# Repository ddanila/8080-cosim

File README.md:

# 8080-cosim

Reconstruction of the Soviet/Estonian Juku E5104 processor board as a physical
PCB and a runnable digital model. Structural Verilog connectivity is checked
against the machine-readable board model with LVS.

## Emulator dependency

The portable C emulator is maintained in [dac-emulation](https://github.com/ddanila/dac-emulation), pinned here as a submodule. After cloning or pulling, run:

```sh
git submodule update --init third_party/dac-emulation
```

Existing `cosim/*.c` build commands still work through forwarding files. Hardware models and their verification stay here. See [the consumer guide](cosim/README.md) for ownership and updating the pin. `bash sync/emulation_check.sh` runs fast native checks without Verilog.

## Current state

The C emulator and structural `juku_top` have ROM-boot and framebuffer
comparison guards, plus keyboard, CPU, FDC, serial and subsystem checks.
The deep cosim guard compares typed CPU-bus events against the C oracle.

The C emulator boots the vendored EKDOS images and reaches disk BASIC
`READY`. [Recorded HDL runs](docs/juku-top-jbasic-verilator-probe.md) also
reached that prompt; current Verilator reruns have a
[build compatibility limitation](sync/README.md#simulator-compatibility).
The bounded boot guard does not establish the full EKDOS/BASIC prompt path.

The production network host is portable C. Linux/macOS, DOS and the Windows
GUI share its core; Janet, Fastboot, NetDisk, N4, snapshots, journals and reset
recovery are implemented. See the [host contract](docs/portable-c-host-plan.md)
and [Windows guide](docs/windows-jukuhost-client.md) for platform qualification
and the latest build.

The physical board is on **DESIGN HOLD / PACKAGE REGENERATION REQUIRED**.
Hidden or conflicting source paths, physical placement, routed copper and
parts decisions remain. The evidence archive is a review package, and the
current Gerber/drill upload ZIP is absent. The
[manufacturing report](docs/replica-manufacturing-readiness.md) owns release
status; [PLAN.md](PLAN.md) lists the remaining work.

The physical shared-DRAM/video slot schedule is not complete. The runnable
framebuffer readout is an abstract oracle, not a proved VIDEO_OUT voltage
waveform. Green behavioral CI and LVS do not establish physical authenticity.

The independent spin-offs are [Jukuravi](spinoffs/jukuravi/README.md),
[VJUGA](spinoffs/minimal-vga/README.md) and
[JukuPoly](spinoffs/jukupoly/README.md). Their physical results and release
criteria are separate from the replica main board.

## Network boot demonstrations

These simulator captures pair the native Juku framebuffer on the left with
timestamped Janet host activity on the right. The simulator is paced at the
approximately 1.7 MHz effective CPU execution rate, the serial links use their
stated baud rates. GIF playback approximates the presentation timeline;
framebuffer timestamp normalization and delay quantization are described in
[the capture guide](media/demos/README.md).

### Stock ROM and CP/Mish CP/M 2.2

The archival 9,600-baud Janet bootstrap is intentionally shown at its original
speed.

### Historical stock-ROM CP/M Plus fast bootstrap

This frozen Python-era V15 capture records the unmodified-ROM experiment whose
compact loader switched to 19,200 baud. The exact JF15 protocol is now
supported by the C host for stock-ROM compatibility, but this historical GIF
itself is not regenerated by the current demo runner.

### Network ROM and CP/M Plus tools

The C8 network-first ROM boots CP/M Plus 3.1 through Fastboot V16 and
demonstrates the resident version report, text utilities, command history, and
control panel.

The capture inputs, dependencies, and regeneration commands are documented in
[`media/demos/README.md`](media/demos/README.md).

## Downstream smoke kit

Use `ghcr.io/ddanila/8080-cosim-smoke-kit:v2` to obtain simulator artifacts
without cloning the repository. The Linux amd64 kit contains the simulator,
static `jukuhost`, frozen Python test fixtures and three ROMs, listed in
[its manifest](.github/smoke-kit/smoke-kit.json) at
`/opt/8080-cosim/smoke-kit.json`.

The `scratch` image has no shell or simulator shared libraries. Copy its
artifacts into a Linux amd64 runtime with the required dynamic loader and
libraries; the [Dockerfile](.github/smoke-kit/Dockerfile) uses Ubuntu 24.04.
The Python fixtures are not standalone executables.

[Publishing](.github/workflows/smoke-kit.yml) runs for selected input changes
on `master` or manual dispatch. It produces the moving `v2` tag and a
`sha-<source commit>` tag. Pin an image digest for reproducible inputs.

## Evidence and source hierarchy

1. Factory drawings, board photographs, dumps, and owner measurements under
   `ref/` are the historical evidence.
2. `kicad/juku.board.json` is the current machine-readable connectivity model.
3. `kicad/juku.kicad_sch`, the PCB files, and fabrication outputs are derived
   from or checked against that model.
4. `hdl/juku_top.v` is independently maintained structural Verilog and is
   checked against the modeled connectivity by `sync/`.
5. `cosim/` and the vendored MAME Juku driver (`ref/mame_juku.cpp`) are behavioral references;
   they are not substitutes for missing physical wiring evidence.

## Board previews

These saved renders show a routed engineering snapshot and may lag the current
PCB. Refresh them with `kicad/render_views.sh` after reviewing board changes;
the [renderer](kicad/render_views.sh) documents its KiCad, font and rasterizer
requirements. Use the PCB and release reports to assess the current design.

| 3D | 2D |
| --- | --- |
|  |  |
|  |  |

## Useful entry points

- [PLAN.md](PLAN.md) — remaining work and release criteria.
- [docs/README.md](docs/README.md) — documentation map and generated-report
  policy.
- [docs/development-workflow.md](docs/development-workflow.md) — canonical
  branch, intermediate commit, and direct-push policy.
- [docs/git-lfs-policy.md](docs/git-lfs-policy.md) — preservation and
  bandwidth policy for original reference photographs.
- [docs/architecture.md](docs/architecture.md) — model boundaries and data flow.
- [docs/source-coverage-audit.md](docs/source-coverage-audit.md) — adopted
  external evidence and remaining source gaps.
- [sync/README.md](sync/README.md) — verification commands.
- [docs/replica-manufacturing-readiness.md](docs/replica-manufacturing-readiness.md)
  — fabrication-package integrity and the current design hold.

## Verification commands

```sh
sync/check.sh
sync/boot_check.sh
sync/cosim_check.sh
python3 scripts/check_documentation_consistency.py
```

`sync/cosim_check.sh` is a deep guard and can take substantially longer than
the other commands. The long reset-to-EKDOS/BASIC and Monitor 3.3 diagnostics
have separate entry points listed in `sync/README.md`.

## Layout

| Path | Purpose |
| --- | --- |
| `ref/` | Factory drawings, photographs, firmware evidence, and external references |
| `kicad/` | Board model, generated schematic, source/routed PCBs with current routing holds, and fabrication tooling |
| `hdl/` | Structural runnable model and device behavior |
| `cosim/` | Independent software emulator/oracle |
| `sync/` | LVS, behavioral comparisons, and subsystem guards |
| `roms/`, `media/` | Vendored preservation inputs with provenance/checksums |
| `docs/` | Current specifications and generated evidence reports |
| `spinoffs/jukupoly/` | Independent Juku CP/M three-tone-plus-percussion music engine, importers, songs, and evidence |
| `spinoffs/minimal-vga/` | Independent VJUGA experiment; not on the replica critical path |

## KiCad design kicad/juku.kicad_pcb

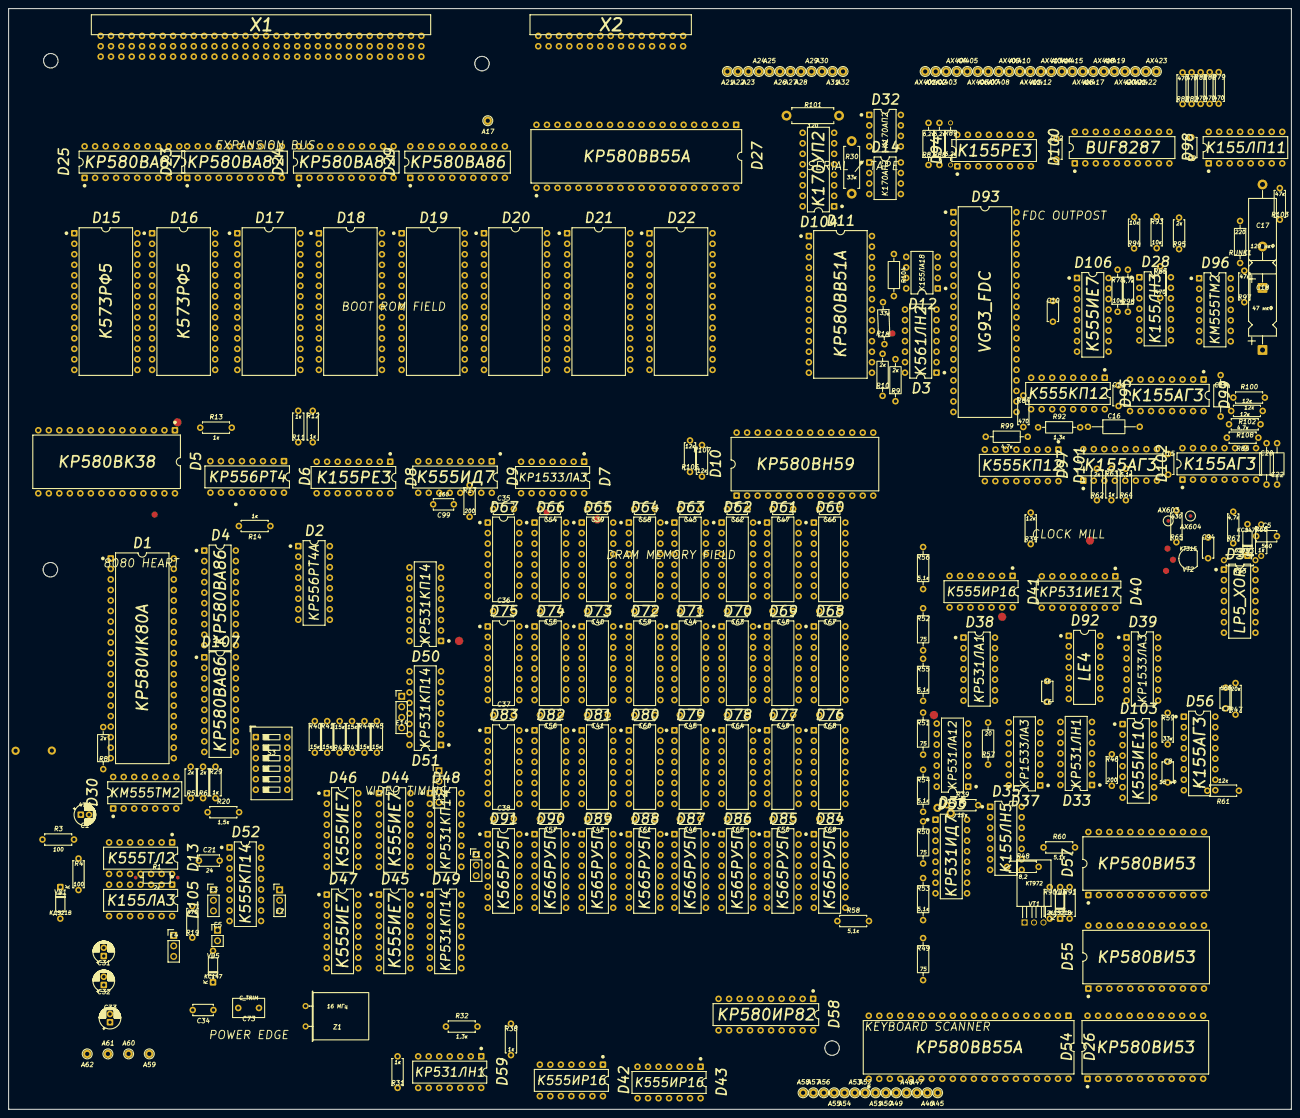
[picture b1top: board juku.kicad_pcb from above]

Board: 2 copper layers, 310.0 x 266.0 mm, 324 parts (0 on the bottom side), 418 nets, no tracks yet.

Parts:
A17, A21, A22, A23, A24, A25, A26, A27, A28, A29, A30, A31, A32, A45, A46, A47, A48, A49, A50, A51, A52, A53, A54, A55, A56, A57, A58, A59, A60, A61, A62: TestPoint_THTPad_D2.0mm_Drill1.0mm
AX401, AX402, AX403, AX404, AX405, AX406, AX407, AX408, AX409, AX410, AX411, AX412, AX413, AX414, AX415, AX416, AX417, AX418, AX419, AX420, AX421, AX422, AX423, AX603, AX604: TestPoint_THTPad_D2.0mm_Drill1.0mm
C1: 47,0; CP_Radial_D5.0mm_P2.00mm
C5, C7: 560; C_Disc_D4.7mm_W2.5mm_P5.00mm
C6: 56; C_Disc_D4.7mm_W2.5mm_P5.00mm
C8: 15 нФ; C_Disc_D4.7mm_W2.5mm_P5.00mm
C9, C10, C11, C12, C15, C34, C94: C_Disc_D4.7mm_W2.5mm_P5.00mm
C16: C_Axial_L5.1mm_D3.1mm_P12.50mm_Horizontal
C17: 120 мкФ; CP_Axial_L18.0mm_D6.5mm_P25.00mm_Horizontal
C18: 47 мкФ; CP_Axial_L18.0mm_D6.5mm_P25.00mm_Horizontal
C19, C20, C22: C_Axial_L5.1mm_D3.1mm_P10.00mm_Horizontal
C21: 24; C_Disc_D4.7mm_W2.5mm_P5.00mm
C31, C32, C33: CP_Radial_D5.0mm_P2.00mm
C35, C36, C37, C38, C39, C40, C41, C42, C43, C44, C45, C46, C47, C48, C49, C50, C54, C55, C56, C57, C58, C59, C60, C61, C62, C63, C64, C65, C66, C67, C68, C69: 0,047; C_Disc_D4.7mm_W2.5mm_P5.00mm
C73: C_TRIM; C_Disc_D7.5mm_W4.4mm_P5.00mm
C99: 160; C_Disc_D4.7mm_W2.5mm_P5.00mm
D1: КР580ИК80А; DIP-40_W15.24mm
D2: КР556РТ4А; DIP-16_W7.62mm
D3: К561ЛН2; DIP-14_W7.62mm
D4, D29, D107: КР580ВА86; DIP-20_W7.62mm
D5: КР580ВК38; DIP-28_W15.24mm
D6: КР556РТ4; DIP-16_W7.62mm
D7, D37, D39: КР1533ЛА3; DIP-14_W7.62mm
D8, D94: К155РЕ3; DIP-16_W7.62mm
D9: К555ИД7; DIP-16_W7.62mm
D10: КР580ВН59; DIP-28_W15.24mm
D11: КР580ВВ51А; DIP-28_W15.24mm
D12: К155ЛА18; DIP-8_W7.62mm
D13: К555ТЛ2; DIP-14_W7.62mm
D14, D32: К170АП2; DIP-8_W7.62mm
D15, D16, D17, D18, D20, D21, D22: К573РФ5; DIP-28_W15.24mm
D19: К573РФ6; DIP-28_W15.24mm
D23, D24, D25: КР580ВА87; DIP-20_W7.62mm
D26, D27: КР580ВВ55А; DIP-40_W15.24mm
D28: К155ЛН3; DIP-14_W7.62mm
D30, D96: КМ555ТМ2; DIP-14_W7.62mm
D33, D59: КР531ЛН1; DIP-14_W7.62mm
D34: LP5_XOR; DIP-14_W7.62mm
D35: К155ЛН5; DIP-14_W7.62mm
D36: КР531ЛА12; DIP-14_W7.62mm
D38: КР531ЛА1; DIP-14_W7.62mm
D40: КР531ИЕ17; DIP-16_W7.62mm
D41, D42, D43: К555ИР16; DIP-14_W7.62mm
D44, D45, D46, D47, D106: К555ИЕ7; DIP-16_W7.62mm
D48, D49, D50, D51: КР531КП14; DIP-16_W7.62mm
D52: К555КП14; DIP-16_W7.62mm
D53: КР531ИД7; DIP-16_W7.62mm
D54, D55, D57: КР580ВИ53; DIP-24_W15.24mm
D56, D97, D99, D102: К155АГ3; DIP-16_W7.62mm
D58: КР580ИР82; DIP-20_W7.62mm
D60, D61, D62, D63, D64, D65, D66, D67, D68, D69, D70, D71, D72, D73, D74, D75, D76, D77, D78, D79, D80, D81, D82, D83: 565РУ3Г; DIP-16_W7.62mm
D84, D85, D86, D87, D88, D89, D90, D91: К565РУ5Г; DIP-16_W7.62mm
D92: LE4; DIP-14_W7.62mm
D93: VG93_FDC; DIP-40_W15.24mm
D95, D101: К555КП12; DIP-16_W7.62mm
D98: К155ЛП11; DIP-16_W7.62mm
D100: BUF8287; DIP-20_W7.62mm
D103: К555ИЕ10; DIP-16_W7.62mm
D104: К170УП2; DIP-16_W7.62mm
D105: К155ЛА3; DIP-14_W7.62mm
E1, E2, E3, E4: PinHeader_1x03_P2.54mm_Vertical
E5: PinHeader_1x02_P2.54mm_Vertical
E13, E14: PinHeader_1x04_P2.54mm_Vertical
R1, R8, R9, R10: 2к; R_Axial_DIN0207_L6.3mm_D2.5mm_P10.16mm_Horizontal
R3, R4: 100; R_Axial_DIN0207_L6.3mm_D2.5mm_P7.62mm_Horizontal
R5, R6, R62, R90, R95: 2к; R_Axial_DIN0207_L6.3mm_D2.5mm_P7.62mm_Horizontal
R11, R12, R13, R14, R29, R31, R38, R63, R66, R91: 1к; R_Axial_DIN0207_L6.3mm_D2.5mm_P7.62mm_Horizontal
R17, R46: 200; R_Axial_DIN0207_L6.3mm_D2.5mm_P7.62mm_Horizontal
R18: 33к; R_Axial_DIN0207_L6.3mm_D2.5mm_P10.16mm_Horizontal
R19, R79, R80, R81, R82, R83, R84, R85: 470; R_Axial_DIN0207_L6.3mm_D2.5mm_P7.62mm_Horizontal
R20: 1,5к; R_Axial_DIN0207_L6.3mm_D2.5mm_P7.62mm_Horizontal
R30: 33к; R_Axial_DIN0411_L9.9mm_D3.6mm_P12.70mm_Horizontal
R32: 1,3к; R_Axial_DIN0207_L6.3mm_D2.5mm_P7.62mm_Horizontal
R33: 620; R_Axial_DIN0207_L6.3mm_D2.5mm_P7.62mm_Horizontal
R34, R39, R61, R100, R102, R105, R107, R108: 12к; R_Axial_DIN0207_L6.3mm_D2.5mm_P7.62mm_Horizontal
R40, R41, R42, R43, R44, R45: 15к; R_Axial_DIN0207_L6.3mm_D2.5mm_P7.62mm_Horizontal
R47: 20к; R_Axial_DIN0207_L6.3mm_D2.5mm_P7.62mm_Horizontal
R48: 8,2; R_Axial_DIN0207_L6.3mm_D2.5mm_P7.62mm_Horizontal
R49, R50, R51, R52: 75; R_Axial_DIN0207_L6.3mm_D2.5mm_P10.16mm_Horizontal
R53, R54, R55, R56: 5,1к; R_Axial_DIN0207_L6.3mm_D2.5mm_P10.16mm_Horizontal
R57: 20; R_Axial_DIN0207_L6.3mm_D2.5mm_P10.16mm_Horizontal
R58, R60, R64: 5,1к; R_Axial_DIN0207_L6.3mm_D2.5mm_P7.62mm_Horizontal
R59: 33к; R_Axial_DIN0207_L6.3mm_D2.5mm_P7.62mm_Horizontal
R65: 430; R_Axial_DIN0207_L6.3mm_D2.5mm_P7.62mm_Horizontal
R67, R86: 4,7к; R_Axial_DIN0207_L6.3mm_D2.5mm_P7.62mm_Horizontal
R78: 10к; R_Axial_DIN0207_L6.3mm_D2.5mm_P10.16mm_Horizontal
R87, R88, R89: 6,2к; R_Axial_DIN0207_L6.3mm_D2.5mm_P10.16mm_Horizontal
R92: 1,3к; R_Axial_DIN0207_L6.3mm_D2.5mm_P10.16mm_Horizontal
R93, R94: 10к; R_Axial_DIN0207_L6.3mm_D2.5mm_P7.62mm_Horizontal
R97, R103: 47к; R_Axial_DIN0207_L6.3mm_D2.5mm_P7.62mm_Horizontal
R98, R99: 4,7к; R_Axial_DIN0207_L6.3mm_D2.5mm_P10.16mm_Horizontal
R101: 120; R_Axial_DIN0411_L9.9mm_D3.6mm_P12.70mm_Horizontal
R104: 470; R_Axial_DIN0207_L6.3mm_D2.5mm_P10.16mm_Horizontal
RUNK1: 220; R_Axial_DIN0207_L6.3mm_D2.5mm_P10.16mm_Horizontal
S3: SW_DIP_SPSTx06_Slide_9.78x17.42mm_W7.62mm_P2.54mm
VD1, VD4: КД521В; D_DO-35_SOD27_P7.62mm_Horizontal
VD3: КС147Г; D_DO-35_SOD27_P7.62mm_Horizontal
VD5: КС147; D_DO-35_SOD27_P7.62mm_Horizontal
VT1: КТ972; TO-126-3_Horizontal_TabDown
VT2: КТ315; TO-92_Inline
W7: A:7 ~24cm insulated wire (cut length held); FACTORY_WIRE_W7
W8: A:8 ~19cm insulated wire; FACTORY_WIRE_W8
W10: A:10 13.5cm insulated wire; FACTORY_WIRE_W10
W11: A:11 ~11.5cm insulated wire (cut length held); FACTORY_WIRE_W11
W14: A:14 ~23cm insulated wire (cut length held); FACTORY_WIRE_W14
W19: A:19 ~9.5cm insulated wire; FACTORY_WIRE_W19
W20: A:20 ~6cm insulated wire; FACTORY_WIRE_W20
X1: CONN_X1
X2: CONN_X2
Z1: 16 МГц; Crystal_HC49-U_Horizontal

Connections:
A0: D1.25, D107.1
A1: D1.26, D107.2
A2: D1.27, D107.3
A3: D1.29, D107.4
A4: D1.30, D107.5
A5: D1.31, D107.6
A6: D1.32, D107.7
A7: D1.33, D107.8
A8: D1.34, D4.8
A9: D1.35, D2.7, D4.7
A10: D1.1, D2.1, D4.1
A11: D1.40, D4.2
A12: D1.37, D2.5, D4.5
A13: D1.38, D4.4
A14: D1.39, D2.3, D4.3
A15: D1.36, D2.6, D4.6
ADR0_N: D23.19, X1.124C
ADR1_N: D23.18, X1.124B
ADR2_N: D23.17, X1.123C
ADR3_N: D23.16, X1.123B
ADR4_N: D23.15, X1.122C
ADR5_N: D23.14, X1.122B
ADR6_N: D23.13, X1.121C
ADR7_N: D23.12, X1.121B
ADR8_N: D24.19, X1.120C
ADR9_N: D24.18, X1.120B
ADRA_N: D24.17, X1.119C
ADRB_N: D24.16, X1.119B
ADRC_N: D24.15, X1.118C
ADRD_N: D24.14, X1.118B
ADRE_N: D24.13, X1.117C
ADRF_N: D24.12, X1.117B
AMWC_N: D29.12, X1.102B
AMW_N: D7.3, D29.2
AVDC: D26.40, R91.2
BA0: D10.27, D11.12, D15.10, D16.10, D17.10, D18.10, D19.10, D20.10, D21.10, D22.10, D23.1, D26.9, D27.9, D48.2, D54.19, D55.19, D57.19, D93.5, D94.10, D107.19
BA1: D15.9, D16.9, D17.9, D18.9, D19.9, D20.9, D21.9, D22.9, D23.2, D26.8, D27.8, D48.14, D54.20, D55.20, D57.20, D93.6, D94.11, D107.18
BA2: D15.8, D16.8, D17.8, D18.8, D19.8, D20.8, D21.8, D22.8, D23.3, D48.11, D107.17
BA3: D15.7, D16.7, D17.7, D18.7, D19.7, D20.7, D21.7, D22.7, D23.4, D48.5, D107.16
BA4: D15.6, D16.6, D17.6, D18.6, D19.6, D20.6, D21.6, D22.6, D23.5, D49.2, D107.15
BA5: D15.5, D16.5, D17.5, D18.5, D19.5, D20.5, D21.5, D22.5, D23.6, D49.14, D107.14
BA6: D15.4, D16.4, D17.4, D18.4, D19.4, D20.4, D21.4, D22.4, D23.7, D49.11, D107.13
BA7: D15.3, D16.3, D17.3, D18.3, D19.3, D20.3, D21.3, D22.3, D23.8, D49.5, D52.2, D107.12
BA8: D4.12, D15.25, D16.25, D17.25, D18.25, D19.25, D20.25, D21.25, D22.25, D24.1, D49.6, D52.5
BA9: D4.13, D15.24, D16.24, D17.24, D18.24, D19.24, D20.24, D21.24, D22.24, D24.2, D48.3
BA10: D4.19, D9.1, D15.21, D16.21, D17.21, D18.21, D19.21, D20.21, D21.21, D22.21, D24.3, D48.6
BA11: D4.18, D6.3, D8.10, D9.2, D15.23, D16.23, D17.23, D18.23, D19.23, D20.23, D21.23, D22.23, D24.4, D48.10
BA12: D4.15, D6.4, D8.11, D9.3, D15.2, D16.2, D17.2, D18.2, D19.2, D20.2, D21.2, D22.2, D24.5, D49.3
BA13: D4.16, D6.7, D8.12, D24.6, D48.13
BA14: D4.17, D6.6, D8.13, D24.7, D49.13
BA15: D4.14, D6.5, D8.14, D24.8, D49.10
C21_R20_SERIES: C21.2, R20.1
CAS: D2.4, D36.1, D38.1, D60.15, D61.15, D62.15, D63.15, D64.15, D65.15, D66.15, D67.15, D68.15, D69.15, D70.15, D71.15, D72.15, D73.15, D74.15, D75.15, D76.15, D77.15, D78.15, D79.15, D80.15, D81.15, D82.15, D83.15, D84.15, D85.15, D86.15, D87.15, D88.15, D89.15, D90.15, D91.15, R57.2, R58.1
CAS_PRE: D36.11, R57.1
CCLCK: D29.19, X1.111C
CLKG_D33: D33.8, D38.9
CLKG_D36: D35.11, D36.6
CLK_123M: D57.9, D103.11
CO0: D44.12, D45.5
CO1: D45.12, D46.5
CO2: D46.12, D47.5
CPU_MUX_G: D48.15, D49.15, D59.6, E13.1, E13.3
CS_D10: D9.15, D10.1
CS_D11: D9.13, D11.11
CS_D26: D9.14, D26.6
CS_D27: D9.12, D27.6
CS_D54: D9.11, D54.21
CS_D55: D9.10, D55.21
CS_D57: D9.9, D57.21
CTR_LD: D34.3, D44.11, D45.11
D3_O4_D6_A6: D3.4, D6.1
D3_O6_D6_A5: D3.6, D6.2
D6_V_ENABLE: D6.13, D6.14, D13.12
D13_4_D105_2: D11.20, D13.4, D30.11, D105.2
D25_T: D7.6, D25.11
D26_PC0_D3_I5: D3.5, D26.14
D26_PC1_D3_I3: D3.3, D26.15
D30_Q2N_D29_AIN7: D29.7, D30.8
D33_6_D36: D33.6, D36.4
D33_CLK_RC: C6.1, D33.9, R46.2
D33_D36: D33.10, D36.10
D33_O4: D33.4, D37.5
D34_RC_DRIVE: C5.1, D34.6
D34_RC_NODE: C5.2, D34.2, R33.1
D34_SIG: D34.11, R63.1
D34_SYNC: D34.8, R62.1
D36_CAS_IN: D36.12, D36.13
D36_D33: D33.11, D36.3
D39Y: D38.10, D38.13, D39.11
D39_MEMCYC: D39.3, D39.4
D39_O8: D39.8, D59.11
D40Q1_D39: D36.5, D39.12, D40.13, D95.11, D95.12, D95.13
D40Q2_D33: D33.5, D40.12, D57.15, D95.3, D95.4
D40QA: D39.13, D40.14, D95.10, R46.1
D40_CTRL_PULL: D40.1, D40.9, R34.2
D42_Q: D35.4, D37.13, D42.10
D43_DS: D42.1, D43.10
D52_Y0: D52.4, E2.1
D52_Y1: D52.7, E3.1
D53_Y0_R49: D53.15, R49.1
D53_Y1_R50: D53.14, R50.1
D53_Y2_R51: D53.13, R51.1
D53_Y3_R52: D53.12, R52.1
D56_C1: C8.2, D56.14
D56_C2: C7.2, D56.6
D56_CLR: D56.3, D56.11, R61.2
D56_Q2N_TAG16: D55.15, D55.18, D56.12
D56_Q2_D34: D34.9, D56.5
D56_QN_D34: D34.10, D56.4
D56_RC1: C8.1, D56.15, R59.1
D56_RC2: C7.1, D56.7, R47.1
D92_NOACC: D39.5, D92.8
D92_RD_NOR: D92.11, D92.12
D92_WR_NOR: D92.6, D92.9, D92.10
D93_TEST_WF_VFOE: D93.22, D93.33
D94_A4_D101_Q0: D94.14, D101.7
D94_D0_BOUNDARY: D94.1, R8.1
D94_D1_D99_A2N: D94.2, D96.11, D99.9, R89.1
D96_TOGGLE_FEEDBACK: D96.2, D96.6
D97_C1_C16: C16.2, D97.14
D97_C2_C19_R86_TARGET: C19.2, D97.6, R86.1
D97_RC1_C16: C16.1, D97.15
D97_RC2_C19_R100: C19.1, D97.7, R100.1
D98_Y1_D28_READY: D28.5, D98.3
D98_Y3_S1_2: D97.2, D98.7
D99_B2_SHEET1_BOUNDARY: D96.13, D99.10
D99_C1_TIMING: C18.2, D99.14
D99_C2_TIMING: C17.2, D99.6
D99_Q1N_BOUNDARY: D93.23, D99.4
D99_Q2N_BOUNDARY: D99.12, D100.9
D99_Q2_BOUNDARY: D99.5, D100.7
D99_RC1_TIMING: C18.1, D99.15, R103.1
D99_RC2_TIMING: C17.1, D99.7, R97.1
D101_D02_R92_R99: D96.9, D101.3, D101.4, D101.5, D101.6, R92.1, R99.2
D102_C1_C22: C22.1, D102.14
D102_C2_C20: C20.1, D102.6
D102_RC1_C22_R102: C22.2, D102.15, R102.1
D102_RC2_C20_R108: C20.2, D102.7, R108.1
D103_CO: D33.1, D103.15
D103_LD: D33.2, D103.9
D105_10_H: D13.13, D105.10, R1.2, X1.107B
D105_MEMW_INV: D30.13, D105.11
D105_WAIT_STAGE: D105.4, D105.5, D105.8
D106_PRESET_HIGH: D106.1, D106.5, D106.9, D106.10, D106.15, R78.1
DAT0_N: D25.19, X1.132C
DAT1_N: D25.18, X1.132B
DAT2_N: D25.17, X1.131C
DAT3_N: D25.16, X1.131B
DAT4_N: D25.15, X1.130C
DAT5_N: D25.14, X1.130B
DAT6_N: D25.13, X1.129C
DAT7_N: D25.12, X1.129B
DB0: D5.18, D10.11, D11.27, D15.11, D16.11, D17.11, D18.11, D19.11, D20.11, D21.11, D22.11, D25.1, D26.34, D27.34, D54.8, D55.8, D57.8, D58.19, D60.2, D68.2, D76.2, D84.2, D93.7
DB1: D5.16, D10.10, D11.28, D15.12, D16.12, D17.12, D18.12, D19.12, D20.12, D21.12, D22.12, D25.2, D26.33, D27.33, D54.7, D55.7, D57.7, D58.18, D61.2, D69.2, D77.2, D85.2, D93.8
DB2: D5.9, D10.9, D11.1, D15.13, D16.13, D17.13, D18.13, D19.13, D20.13, D21.13, D22.13, D25.3, D26.32, D27.32, D54.6, D55.6, D57.6, D58.17, D62.2, D70.2, D78.2, D86.2, D93.9
DB3: D5.20, D10.8, D11.2, D15.15, D16.15, D17.15, D18.15, D19.15, D20.15, D21.15, D22.15, D25.4, D26.31, D27.31, D54.5, D55.5, D57.5, D58.16, D63.2, D71.2, D79.2, D87.2, D93.10
DB4: D5.5, D10.7, D11.5, D15.16, D16.16, D17.16, D18.16, D19.16, D20.16, D21.16, D22.16, D25.5, D26.30, D27.30, D54.4, D55.4, D57.4, D58.15, D64.2, D72.2, D80.2, D88.2, D93.11
DB5: D5.13, D10.6, D11.6, D15.17, D16.17, D17.17, D18.17, D19.17, D20.17, D21.17, D22.17, D25.6, D26.29, D27.29, D54.3, D55.3, D57.3, D58.14, D65.2, D73.2, D81.2, D89.2, D93.12
DB6: D5.11, D10.5, D11.7, D15.18, D16.18, D17.18, D18.18, D19.18, D20.18, D21.18, D22.18, D25.7, D26.28, D27.28, D54.2, D55.2, D57.2, D58.13, D66.2, D74.2, D82.2, D90.2, D93.13
DB7: D5.7, D10.4, D11.8, D15.19, D16.19, D17.19, D18.19, D19.19, D20.19, D21.19, D22.19, D25.8, D26.27, D27.27, D54.1, D55.1, D57.1, D58.12, D67.2, D75.2, D83.2, D91.2, D93.14
DBIN: D1.17, D105.9
DBIN_GATED: D5.4, D105.6
DC0: D1.10, D5.19
DC1: D1.9, D5.17
DC2: D1.8, D5.10
DC3: D1.7, D5.21
DC4: D1.3, D5.6
DC5: D1.4, D5.15
DC6: D1.5, D5.12
DC7: D1.6, D5.8
E2_COM: D53.1, E2.2
E3_COM: D53.2, E3.2
FDC_CLK: D93.24, D95.7
FDC_CS_N: D9.7, D93.3, D94.15
FDC_DDEN: D26.13, D93.37, D95.14, R92.2
FDC_DIR_TO_D100: D93.16, D100.1
FDC_DRIVE_SIZE_5_8: D26.17, D95.2
FDC_DRQ: D28.11, D93.38, R94.1
FDC_DSEL_IN: D26.12, D28.1
FDC_EARLY_SEL: D93.17, D101.2
FDC_HLD_TO_D100: D93.28, D99.2, D100.3
FDC_IMDRG: D26.38, D101.1
FDC_INDEX_STATUS: D93.35, D98.5
FDC_INTRQ: D28.13, D93.39, R93.1
FDC_IRQ_CONDITIONED_N: D28.10, D28.12, D96.10, D96.12, R95.1
FDC_LATE_SEL: D93.18, D101.14
FDC_MOTOR_EN: D26.16, D99.11
FDC_PRECOMP_WRDATA: D100.6, D101.9
FDC_RAW_READ: D93.27, D97.4, D106.11
FDC_RCLK: D93.26, D96.5
FDC_READY: D28.6, D93.32, R84.1
FDC_RESET_N: D13.8, D93.19
FDC_RE_N: D93.4, D94.3, R88.1
FDC_SEPARATOR_CLOCK: D95.9, D106.4
FDC_SIDE_SEL: D26.11, D100.8
FDC_STEP_TO_D100: D93.15, D100.2
FDC_TG43_TO_D100: D93.29, D100.4
FDC_TR00_STATUS: D93.34, D98.11
FDC_WDATA_DELAY_IN: D93.31, D97.10
FDC_WE_N: D93.2, D94.4, R87.1
FDC_WG_TO_D100: D93.30, D100.5
FDC_WPRT_STATUS: D93.36, D98.13
FRAME_INT: D10.23, D35.8, R60.1
GND: A62.1, AX406.1, AX604.1, C1.2, C6.2, C31.2, C32.2, C33.1, C34.2, C35.2, C36.2, C37.2, C38.2, C39.2, C40.2, C41.2, C42.2, C43.2, C44.2, C45.2, C46.2, C47.2, C48.2, C49.2, C50.2, C54.1, C55.1, C56.1, C57.1, C58.1, C59.1, C60.1, C61.1, C62.1, C63.1, C64.1, C65.1, C66.1, C67.1, C68.1, C69.1, C99.2, D1.2, D1.13, D2.8, D2.13, D2.14, D3.7, D4.9, D4.10, D5.14, D5.22, D6.8, D7.7, D8.8, D9.8, D10.14, D11.4, D12.4, D13.7, D14.1, D14.4, D15.14, D16.14, D17.14, D18.14, D19.14, D20.14, D21.14, D22.14, D23.9, D23.10, D24.9, D24.10, D25.9, D25.10, D26.7, D27.7, D28.7, D29.9, D29.10, D30.7, D32.4, D33.7, D34.5, D34.7, D35.7, D36.7, D37.7, D38.2, D38.7, D39.2, D39.7, D40.8, D41.2, D41.3, D41.4, D41.5, D41.7, D42.7, D43.1, D43.7, D44.1, D44.8, D44.9, D44.10, D44.14, D44.15, D45.1, D45.8, D45.14, D45.15, D46.8, D46.14, D47.8, D47.14, D48.8, D49.8, D50.8, D51.8, D52.8, D52.15, D53.3, D53.5, D53.8, D54.12, D55.12, D56.1, D56.8, D56.9, D57.12, D58.10, D59.7, D60.16, D61.16, D62.16, D63.16, D64.16, D65.16, D66.16, D67.16, D68.16, D69.16, D70.16, D71.16, D72.16, D73.16, D74.16, D75.16, D76.16, D77.16, D78.16, D79.16, D80.16, D81.16, D82.16, D83.16, D84.16, D85.16, D86.16, D87.16, D88.16, D89.16, D90.16, D91.16, D92.7, D93.20, D94.8, D95.1, D95.8, D95.15, D96.7, D97.1, D97.8, D97.9, D98.1, D98.8, D98.15, D99.1, D99.3, D99.8, D100.10, D101.8, D101.13, D101.15, D102.1, D102.8, D102.9, D103.5, D103.6, D103.8, D104.7, D104.8, D105.7, D106.8, D106.14, D107.9, D107.10, E13.4, E14.4, R30.2, R33.2, R53.2, R54.2, R55.2, R56.2, R58.2, R64.2, R65.2, R99.1, R105.2, R107.2, S3.7, S3.8, S3.9, S3.10, S3.11, S3.12, VD3.1, VD5.1
HLDA: D1.21, D5.2
INHIB_N: D29.17, X1.106B
INHIB_STATUS_BOUNDARY: D7.5, D29.3
INT4_RAW: D12.6, D12.7, X1.114C
INT6_RAW: D3.1, R10.1, X1.113C
INT7_RAW: D3.13, R9.1, X1.113B
INTA: D5.23, D10.26
INTR: D1.14, D10.17
IOM_N: D29.18, X1.109B
IORC_N: D2.2, D29.16, X1.106C
IORD: D5.25, D7.9, D10.3, D11.13, D26.5, D27.5, D29.4, D54.22, D55.22, D57.22, D94.12
IOWC_N: D29.15, X1.105B
IOWR: D10.2, D11.10, D26.36, D27.36, D29.5, D54.23, D55.23, D57.23, D94.13, D105.3
IOWR_RAW_N: D5.27, D7.10
IO_CYCLE_H: D6.15, D7.8, D105.1
IR7: D3.12, D10.25
KBD_CONTRDAT: A50.1, D26.22
KBD_CTRL: A51.1, D26.25
KBD_FK: A55.1, D26.18
KBD_K0: A57.1, D26.19
KBD_K1: A56.1, D26.20
KBD_K2: A58.1, D26.21
KBD_SC0: A48.1, D26.4
KBD_SC1: A47.1, D26.3
KBD_SC2: A46.1, D26.2
KBD_SC3: A45.1, D26.1
KBD_SHIFT: A52.1, D26.24
KBD_STB: A49.1, D26.37
LATCH_A: D37.1, D41.12
LATCH_B: D37.2, D40.11, D50.15, D51.15, D54.9, D54.15, D54.18, D59.5, D92.2, D92.3, D95.5, D95.6, E14.1, E14.3
LATCH_PRE: D33.13, D37.3
LATCH_SIG: D33.12, D38.5, D39.9
LOAD_PRE: D38.6, D59.13
LOAD_VID: D42.6, D43.6, D59.12
M5V_DERIVED: D1.11, E5.1, R19.2, VD5.2
M12V: A59.1, C33.2, D14.5, D32.5, R19.1, X1.110A, X1.111A
MA0: D48.4, D50.4, D60.6, D61.6, D62.6, D63.6, D64.6, D65.6, D66.6, D67.6, D68.6, D69.6, D70.6, D71.6, D72.6, D73.6, D74.6, D75.6, D76.6, D77.6, D78.6, D79.6, D80.6, D81.6, D82.6, D83.6, D84.6, D85.6, D86.6, D87.6, D88.6, D89.6, D90.6, D91.6
MA1: D48.12, D50.12, D60.12, D61.12, D62.12, D63.12, D64.12, D65.12, D66.12, D67.12, D68.12, D69.12, D70.12, D71.12, D72.12, D73.12, D74.12, D75.12, D76.12, D77.12, D78.12, D79.12, D80.12, D81.12, D82.12, D83.12, D84.12, D85.12, D86.12, D87.12, D88.12, D89.12, D90.12, D91.12
MA2: D48.9, D50.9, D60.13, D61.13, D62.13, D63.13, D64.13, D65.13, D66.13, D67.13, D68.13, D69.13, D70.13, D71.13, D72.13, D73.13, D74.13, D75.13, D76.13, D77.13, D78.13, D79.13, D80.13, D81.13, D82.13, D83.13, D84.13, D85.13, D86.13, D87.13, D88.13, D89.13, D90.13, D91.13
MA3: D48.7, D50.7, D60.5, D61.5, D62.5, D63.5, D64.5, D65.5, D66.5, D67.5, D68.5, D69.5, D70.5, D71.5, D72.5, D73.5, D74.5, D75.5, D76.5, D77.5, D78.5, D79.5, D80.5, D81.5, D82.5, D83.5, D84.5, D85.5, D86.5, D87.5, D88.5, D89.5, D90.5, D91.5
MA4: D49.4, D51.4, D60.10, D61.10, D62.10, D63.10, D64.10, D65.10, D66.10, D67.10, D68.10, D69.10, D70.10, D71.10, D72.10, D73.10, D74.10, D75.10, D76.10, D77.10, D78.10, D79.10, D80.10, D81.10, D82.10, D83.10, D84.10, D85.10, D86.10, D87.10, D88.10, D89.10, D90.10, D91.10
MA5: D49.12, D51.12, D60.7, D61.7, D62.7, D63.7, D64.7, D65.7, D66.7, D67.7, D68.7, D69.7, D70.7, D71.7, D72.7, D73.7, D74.7, D75.7, D76.7, D77.7, D78.7, D79.7, D80.7, D81.7, D82.7, D83.7, D84.7, D85.7, D86.7, D87.7, D88.7, D89.7, D90.7, D91.7
MA6: D49.9, D51.9, D60.11, D61.11, D62.11, D63.11, D64.11, D65.11, D66.11, D67.11, D68.11, D69.11, D70.11, D71.11, D72.11, D73.11, D74.11, D75.11, D76.11, D77.11, D78.11, D79.11, D80.11, D81.11, D82.11, D83.11, D84.11, D85.11, D86.11, D87.11, D88.11, D89.11, D90.11, D91.11, E1.3
MA7: D49.7, D51.7, D60.9, D61.9, D62.9, D63.9, D64.9, D65.9, D66.9, D67.9, D68.9, D69.9, D70.9, D71.9, D72.9, D73.9, D74.9, D75.9, D76.9, D77.9, D78.9, D79.9, D80.9, D81.9, D82.9, D83.9, D84.9, D85.9, D86.9, D87.9, D88.9, D89.9, D90.9, D91.9, E1.2
MEMR: D5.24, D15.22, D16.22, D17.22, D18.22, D19.22, D20.22, D21.22, D22.22, D29.6, D33.3, D92.13, W11.1
MEMR_D7: D7.1, W11.2
MEMW: D5.26, D7.4, D29.8, D36.9, D92.4, D105.12, D105.13, W19.1
MEMW_D7P2: D7.2, W19.2
MRC_N: D29.14, X1.104C
MWC_N: D29.13, X1.104B
OSC: C73.2, D40.2, D59.2, D59.3
OSC_FB: D59.9, R31.1, R32.1, Z1.1
OSC_PRE: D59.1, D59.8, R31.2
P5V: A53.1, A54.1, A61.1, AX412.1, AX413.1, C31.1, C34.1, D1.20, D2.16, D3.14, D4.11, D4.20, D5.28, D6.16, D7.14, D8.16, D9.16, D10.16, D10.28, D11.26, D12.8, D13.14, D15.1, D15.26, D15.27, D15.28, D16.1, D16.26, D16.27, D16.28, D17.1, D17.26, D17.27, D17.28, D18.1, D18.26, D18.27, D18.28, D19.1, D19.26, D19.27, D19.28, D20.1, D20.26, D20.27, D20.28, D21.1, D21.26, D21.27, D21.28, D22.1, D22.26, D22.27, D22.28, D23.11, D23.20, D24.11, D24.20, D25.20, D26.26, D27.26, D28.14, D29.11, D29.20, D30.14, D33.14, D34.1, D34.13, D34.14, D35.14, D36.14, D37.14, D38.14, D39.14, D40.7, D40.10, D40.16, D41.1, D41.8, D41.14, D42.14, D43.14, D44.4, D44.16, D45.4, D45.16, D46.4, D46.16, D47.4, D47.16, D48.16, D49.16, D50.16, D51.16, D52.16, D53.16, D54.11, D54.24, D55.11, D55.24, D56.16, D57.11, D57.14, D57.16, D57.24, D58.20, D59.14, D92.14, D93.21, D94.16, D95.16, D96.14, D97.16, D98.16, D99.16, D100.20, D101.16, D102.16, D103.1, D103.3, D103.4, D103.7, D103.10, D103.16, D104.15, D105.14, D106.16, D107.11, D107.20, E1.1, E4.3, E13.2, E14.2, R1.1, R3.1, R5.1, R6.1, R8.2, R9.2, R10.2, R11.1, R12.1, R13.1, R14.1, R34.1, R38.2, R39.2, R40.2, R41.2, R42.2, R43.2, R44.2, R45.2, R47.2, R59.2, R60.2, R61.1, R78.2, R79.2, R80.2, R81.2, R82.2, R83.2, R84.2, R85.2, R86.2, R87.2, R88.2, R89.2, R93.2, R94.2, R95.2, R97.2, R98.2, R100.2, R101.2, R102.2, R103.2, R104.2, R108.2, VD1.1, VT1.2, VT2.2, X1.101A, X1.102A, X1.103A, X1.107A, X1.108A, X1.108B, X1.108C, X2.227, X2.229, X2.230
P12V: A60.1, C32.1, D1.28, D14.8, D32.8, D93.40, E4.1, R66.1, X1.131A, X1.132A
PHI1: D1.22, D48.1, D49.1, E2.3, W7.1
PHI1_D35: D35.10, W7.2
PHI2: D1.15, E3.3, W14.1
PHI2TTL: D29.1, D30.3, D39.1, D53.4
PHI2_D35: D35.12, W14.2
PIT_BAUD: D11.9, D11.25, D57.10
PIT_HCHAIN: D54.10, D54.14, D54.16, D55.9
PIT_HSYNC_DSL: D54.17, D56.10
PIT_VCHAIN: D55.10, D55.14, D55.16
POF: D26.10, D35.3, D35.5, R39.1
PRECOMP_CASCADE_1: D97.12, D102.10
PRECOMP_CASCADE_2: D102.2, D102.12
PRECOMP_TAP_1: D97.5, D101.10
PRECOMP_TAP_2: D101.11, D102.5
PRECOMP_TAP_3: D101.12, D102.13
PROM_EN: D7.11, D7.13, R17.2
PST_CLK: D44.5, D59.4, R32.2
RAIL12: D68.4, D69.4, D70.4, D71.4, D72.4, D73.4, D74.4, D75.4, R51.2, R55.1
RAIL13: D76.4, D77.4, D78.4, D79.4, D80.4, D81.4, D82.4, D83.4, R50.2, R54.1
RAIL14: D84.4, D85.4, D86.4, D87.4, D88.4, D89.4, D90.4, D91.4, R49.2, R53.1
RAIL_G: C35.1, C36.1, C37.1, C38.1, C39.1, C40.1, C41.1, C42.1, C43.1, C44.1, C45.1, C46.1, C47.1, C48.1, C49.1, C50.1, D60.8, D61.8, D62.8, D63.8, D64.8, D65.8, D66.8, D67.8, D68.8, D69.8, D70.8, D71.8, D72.8, D73.8, D74.8, D75.8, D76.8, D77.8, D78.8, D79.8, D80.8, D81.8, D82.8, D83.8, D84.8, D85.8, D86.8, D87.8, D88.8, D89.8, D90.8, D91.8, E4.2
RAIL_H: C54.2, C55.2, C56.2, C57.2, C58.2, C59.2, C60.2, C61.2, C62.2, C63.2, C64.2, C65.2, C66.2, C67.2, C68.2, C69.2, D60.1, D61.1, D62.1, D63.1, D64.1, D65.1, D66.1, D67.1, D68.1, D69.1, D70.1, D71.1, D72.1, D73.1, D74.1, D75.1, D76.1, D77.1, D78.1, D79.1, D80.1, D81.1, D82.1, D83.1, D84.1, D85.1, D86.1, D87.1, D88.1, D89.1, D90.1, D91.1, E5.2
RAM_OUT_EN: D13.2, D37.4
RAM_RD_OE: D37.6, D58.9
RAS: D60.4, D61.4, D62.4, D63.4, D64.4, D65.4, D66.4, D67.4, R52.2, R56.1
RDO0: D43.2, D58.1, D60.14, D68.14, D76.14, D84.14
RDO1: D43.3, D58.2, D61.14, D69.14, D77.14, D85.14
RDO2: D43.4, D58.3, D62.14, D70.14, D78.14, D86.14
RDO3: D43.5, D58.4, D63.14, D71.14, D79.14, D87.14
RDO4: D42.2, D58.5, D64.14, D72.14, D80.14, D88.14
RDO5: D42.3, D58.6, D65.14, D73.14, D81.14, D89.14
RDO6: D42.4, D58.7, D66.14, D74.14, D82.14, D90.14
RDO7: D42.5, D58.8, D67.14, D75.14, D83.14, D91.14
READY: D1.23, R29.2
READY_D: D2.12, D30.2, R6.2
READY_Q: D30.5, R29.1
RESET: D1.12, D11.21, D13.6, D13.9, D26.35, D27.35
RESIN: C21.1, D13.5, R4.2
RES_RC: A17.1, C1.1, R3.2, R4.1, VD1.2
REV: D6.10, D9.4, D9.5, R13.2
ROE: D6.9, D13.1, D92.1, R14.2
ROM_CS_4000: D8.4, D22.20
ROM_CS_6000: D8.3, D21.20
ROM_CS_8000: D8.2, D20.20
ROM_CS_A000: D8.1, D19.20
ROM_CS_D15: D8.5, D15.20
ROM_CS_D16: D8.6, D16.20
ROM_CS_EXP17: D8.7, D17.20
ROM_CS_EXP18: D8.9, D18.20
ROM_SEL: D6.12, D8.15, R11.2
S3_1: D45.10, R40.1, S3.1
S3_2: D45.9, R41.1, S3.2
S3_3: D46.15, D47.15, R42.1, S3.3
S3_4: D46.1, D47.1, R43.1, S3.4
S3_5: D46.10, D47.10, R44.1, S3.5
S3_6: D46.9, D47.9, R45.1, S3.6
SEP_D28_CLK: D28.8, D96.3, R85.1
SEP_D106_Q3: D28.9, D106.7
SER_CTS_N: D11.17, D104.12
SER_DSR_N: D11.22, D104.11
SER_DTR: D11.24, D32.2
SER_RTS: D11.23, D32.3
SER_RXD: D11.3, D104.13
SER_TXD: D3.9, D3.11, D11.19, D14.3, R18.2
SER_TXD_INV: D3.8, D12.1, D12.2
SHIFT_G: D35.6, D41.9, D42.8, D43.8, R38.1
SND_BASE: R90.2, VD4.2, VT1.3
SND_CLAMP: R91.1, VD4.1
SND_OUT: R48.1, VT1.1
SOUND: D57.13, R90.1
SOUND_CLAMP: R66.2, R67.1, VD3.2
STSTB: D5.1, W8.1
STSTB_D38: D30.1, D30.4, D30.10, D30.12, D38.8, R5.2, W8.2
SYNC: D1.19, D7.12, D38.12
S_CTS: A25.1, D104.5
S_DSR: A26.1, D104.6
S_DTP: A31.1, D32.7
S_OC: A22.1, A32.1, D12.3, R18.1, R30.1
S_RTS: A30.1, D32.6
S_SIN: A24.1, D104.4
S_SOUT: A29.1, D14.6
S_TTL: A23.1, W20.1
S_TTL_D3: D3.10, W20.2
TIMING_TAG2: D34.4, D38.4
TIMING_TAG17: D36.2, D41.6
USART_RXRDY_IRQ: D10.20, D11.14
USART_TXRDY_IRQ: D10.21, D11.15
V3_RC: C99.1, D9.6, R17.1
VA0: D44.3, D50.2
VA1: D44.2, D50.14
VA2: D44.6, D50.11
VA3: D44.7, D50.5
VA4: D45.3, D51.2
VA5: D45.2, D51.14
VA6: D45.6, D51.11
VA7: D45.7, D51.5, D52.3
VA8: D46.3, D51.6, D52.6
VA9: D46.2, D50.3
VA10: D46.6, D50.6
VA11: D46.7, D50.10
VA12: D47.3, D51.3
VA13: D47.2, D50.13
VA14: D47.6, D51.13
VA15: D47.7, D51.10
VERT_RTR: D35.9, D55.13, D57.18
VERT_SYNC: D55.17, D56.2
VIDEO_OUT: R65.1, VT2.1
VID_CPU_SEL: D39.6, D52.1, D53.6
VID_HI_LD: D46.11, D47.11
VID_MIX1: D34.12, D37.11
VT2_BASE: R62.2, R63.2, R64.1, VT2.3
W10_QA_SEL: D41.13, W10.1
W10_QA_SEL_D50: D50.1, D51.1, W10.2
WR: D1.18, D5.3, D13.3
WREQ_N: D2.15, D6.11, D92.5, D96.1, D96.4, D97.3, D97.11, D102.3, D102.11, R12.2, X1.107C
W_RAIL16: D36.8, D60.3, D61.3, D62.3, D63.3, D64.3, D65.3, D66.3, D67.3, D68.3, D69.3, D70.3, D71.3, D72.3, D73.3, D74.3, D75.3, D76.3, D77.3, D78.3, D79.3, D80.3, D81.3, D82.3, D83.3, D84.3, D85.3, D86.3, D87.3, D88.3, D89.3, D90.3, D91.3
X2_IRQ0: D10.18, D12.5, R104.1, R105.1, X2.214
X2_PA0: D27.4, X2.208
X2_PA1: D27.3, X2.206
X2_PA2: D27.2, X2.201
X2_PA3: D27.1, X2.202
X2_PA4: D27.40, X2.204
X2_PA5: D27.39, X2.203
X2_PA6: D27.38, X2.205
X2_PA7: D27.37, X2.207
X2_PB0: D27.18, X2.221
X2_PB1: D27.19, X2.223
X2_PB2: D27.20, X2.225
X2_PB3: D27.21, X2.226
X2_PB4: D27.22, X2.224
X2_PB5: D27.23, X2.222
X2_PB6: D27.24, X2.220
X2_PB7: D10.19, D27.25, R107.1, X2.218
X2_PC0: D27.14, X2.213
X2_PC1: D27.15, X2.215
X2_PC2: D27.16, X2.217
X2_PC3: D27.17, X2.219
X2_PC4: D27.13, X2.211
X2_PC5: D27.12, X2.212
X2_PC6: D27.11, X2.209
X2_PC7: D27.10, X2.210
X3_HARNESS_1: A21.1, R101.1
X4_DIR_N: AX416.1, D100.19
X4_DSEL0_N: AX422.1, D28.4
X4_DSEL1_N: AX421.1, D28.2, D28.3, R98.1
X4_HLOAD_N: AX417.1, D100.17
X4_INDEX_N: AX415.1, D98.4, R81.1
X4_MOTOR_ON_N: AX419.1, D100.13
X4_RD_DATA: AX423.1, D98.6, R79.1
X4_READY_N: AX408.1, D98.2, R83.1
X4_SIDE_SEL: AX420.1, D100.12
X4_STEP_N: AX409.1, D100.18
X4_TG43: AX410.1, D100.16
X4_TR00_N: AX414.1, D98.12, R80.1
X4_WR_DATA_N: AX411.1, D100.14
X4_WR_GATE_N: AX418.1, D100.15
X4_WR_PROTECT_N: AX407.1, D98.14, R82.1
XTAL16M: D37.12, D39.10, D42.9, D43.9, D103.2
XTAL_TRIM: C73.1, Z1.2

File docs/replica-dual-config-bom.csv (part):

action,type,value,authentic_part,functional_substitute,board_positions,populate_now,leave_empty,refs,populated_refs,notes
circuit-review,AP2,,К170АП2,RS-232/line-driver substitute required; verify +/-12 V interface,2,2,0,"D14, D32","D14, D32",
circuit-review,C_ELEC,,radial electrolytic,"modern electrolytic matching measured body, lead spacing, value, voltage, and polarity",3,3,0,"C31, C32, C33","C31, C32, C33",
circuit-review,C_KM,,КМ ceramic capacitor,modern ceramic capacitor with matching value/voltage/lead spacing,31,9,22,"C9, C10, C11, C12, C15, C16, C19, C34, C74, C75, C76, C77, C78, C82, C83, C84, C85, C86, ... (+13)","C9, C10, C11, C12, C15, C16, C19, C34, C94",
circuit-review,C_KM,,КМ ceramic capacitor,modern ceramic capacitor with matching value/voltage/lead spacing,1,1,0,C20,C20,"Sheet 3 specifies 22 pF nominal; owner angles show bare 22 and ±5% on the body, but the unit is unverified. Confirm capacitance before sourcing."
circuit-review,C_KM,,КМ ceramic capacitor,modern ceramic capacitor with matching value/voltage/lead spacing,1,1,0,C22,C22,"Sheet 3 specifies 22 pF nominal; later owner angles show bare 22 and ±10% on the body, but the unit is unverified. The May face reads М75, the negative 75 ppm/°C ceramic temperature-stability group. Confirm capacitance before sourcing."
circuit-review,C_KM,"0,047","КМ ceramic capacitor 0,047",modern ceramic capacitor with matching value/voltage/lead spacing,4,4,0,"C38, C42, C46, C50","C38, C42, C46, C50","Factory placement/population is closed, but exact target capacitance, tolerance, and voltage remain unread; do not source the final part from the functional 0,047 model value."
circuit-review,C_KM,"0,047","КМ ceramic capacitor 0,047",modern ceramic capacitor with matching value/voltage/lead spacing,6,0,6,"C51, C52, C53, C70, C71, C72",,"Target placement, population, capacitance, tolerance, and voltage remain unresolved; do not fabricate or source this position from the retired fit-to-space coordinate or functional 0,047 model value."
circuit-review,C_KM,56,КМ ceramic capacitor 56,modern ceramic capacitor with matching value/voltage/lead spacing,1,0,1,C29,,"Exact source prints bare 56 without a unit; the native-sheet convention reads values below 1000 as pF, giving nominal 56 pF. Owner population and pads remain open."
circuit-review,C_KM,560,КМ ceramic capacitor 560,modern ceramic capacitor with matching value/voltage/lead spacing,1,1,0,C5,C5,"Exact source nominal 560 pF; no body is visible at the factory C5 site in May/July owner photos, and native photo reread separates the upper D34.2/R33-left and lower D34.6 joints. Identify C5 pads and population history before fitting."
circuit-review,C_TRIM,,trimmer capacitor,modern trimmer capacitor matching footprint/value,1,1,0,C73,C73,
circuit-review,Q_KT13,,КТ315,modern E-C-B transistor selected for the video role and KT-13 pad row,1,1,0,VT2,VT2,
circuit-review,Q_KT27,,КТ972,modern E-C-B TO-126 transistor selected for the beeper role,1,1,0,VT1,VT1,
circuit-review,R_AXIAL,12к,axial resistor 12к,"modern axial resistor, matching value and power rating",2,0,2,"R15, R16",,Source 12 kOhm and ground return; owner return rail and isolated body value require measurement.
circuit-review,R_AXIAL,20к,axial resistor 20к,"modern axial resistor, matching value and power rating",1,0,1,R2,,PCB pad locations and target-body continuity are pending; exact .009 value and drawn branch are captured in the source model.
circuit-review,R_AXIAL,2к,axial resistor 2к,"modern axial resistor, matching value and power rating",1,0,1,R7,,PCB pad locations and target-body continuity are pending; exact .009 value and drawn branch are captured in the source model.
circuit-review,R_AXIAL,330,axial resistor 330,"modern axial resistor, matching value and power rating",1,0,1,R35,,Source 330 ohms and owner 330R body agree; calibrated owner pad geometry is pending.
circuit-review,R_AXIAL,360,axial resistor 360,"modern axial resistor, matching value and power rating",2,0,2,"R36, R37",,"Exact .009 360-ohm phase pull-up; owner body begins 360, but pad nets and isolated value need measurement."
circuit-review,R_AXIAL,470,axial resistor 470,"modern axial resistor, matching value and power rating",1,1,0,R104,R104,"Exact .009 R104 470-ohm D12.5 open-collector pull-up; owner photos close both local D12 links and locate the footprint; installed resistance, known +5 V rail, and remote X2 continuity pending."
circuit-review,R_AXIAL,620,axial resistor 620,"modern axial resistor, matching value and power rating",1,1,0,R33,R33,"Exact source and two independent К62 owner marking reads agree on 620 ohms, but native photos separate the D34.2/R33-left upper joint from the D34.6 lower joint. Meter R33 and inspect the bare C5 site before fitting the pulse shaper."
circuit-review,R_AXIAL,910,axial resistor 910,"modern axial resistor, matching value and power rating",1,0,1,R106,,Exact source prints 910 ohms; owner body in this position reads 510R on two dates. Measure before physical-value adoption.
circuit-review,UP2,,К170УП2,RS-232/line-receiver substitute required; verify +/-12 V interface,1,1,0,D104,D104,
leave-empty,C_KM,"0,047","КМ ceramic capacitor 0,047",modern ceramic capacitor with matching value/voltage/lead spacing,28,0,28,"C35, C36, C37, C39, C40, C41, C43, C44, C45, C47, C48, C49, C54, C55, C56, C57, C58, C59, ... (+10)",,"Target-assembly DNP; retain schematic intent and the fabricated footprint, but do not fit the part."
leave-empty,EPROM8K,,К573РФ6,"2764 / 27C64 / M2764 EPROM, programmed per ROM split",1,0,1,D19,,Only D15/D16 are populated in the .009 functional build; D17-D22 are expansion/empty sockets.
leave-empty,RU5,,К565РУ5Г / 565РУ5Г,Mostek MK4564-12 dual-in-line option; E4 2-3/+5 V required; bench-test received parts,24,0,24,"D60, D61, D62, D63, D64, D65, D66, D67, D68, D69, D70, D71, D72, D73, D74, D75, D76, D77, ... (+6)",,D84-D91 are populated for the 64 KB .158/.009 target; D60-D83 are empty expansion sockets. The guarded MK4564-12 static contract is package/electrically eligible only with E4 2-3/+5 V; receipt and board timing tests remain.
mechanical-review,C_ELEC,"47,0","opposite-end-lead metal-can electrolytic (owner candidate) 47,0","modern electrolytic matching measured body, lead spacing, value, voltage, and polarity",1,1,0,C1,C1,"Owner C1 is an opposite-end-lead metal can with about 20 mm vertical joint span; upper lead photo-joins D13.7/GND, lower lead is marked +. Source PCB still uses a 2 mm radial footprint. Confirm hole coordinates and lower reset-net path, then select a matching footprint and part before sourcing."
mechanical-review,DISPLAY_CONN,,bracket display connector X6; exact mechanical fit pending,select exact substitute after circuit review,1,1,0,X6,X6,
mechanical-review,EXPANSION_CONN,,СНП59-96 Р-20-2-В,select exact substitute after circuit review,1,1,0,X1,X1,
mechanical-review,JUMPER2,,wire/link,select exact substitute after circuit review,1,1,0,E5,E5,
mechanical-review,JUMPER3,,wire/link,select exact substitute after circuit review,4,4,0,"E1, E2, E3, E4","E1, E2, E3, E4",
mechanical-review,JUMPER4,,wire/link,select exact substitute after circuit review,2,2,0,"E13, E14","E13, E14",
mechanical-review,KBD_CONN,,keyboard connector,select exact substitute after circuit review,1,1,0,X9,X9,
mechanical-review,PAR_CONN,,СНП59-30-23-В / parallel connector,select exact substitute after circuit review,1,1,0,X2,X2,
mechanical-review,POWER_CONN,,СНО51-30/56х9В-23 power connector,select exact substitute after circuit review,1,1,0,X8,X8,
mechanical-review,SERIAL_CONN,,РГ1Н-1-4 12-contact serial socket (cable mate РШ2Н-1-23/-24),select exact substitute after circuit review,1,1,0,X3,X3,
mechanical-review,SW,,switch,select exact substitute after circuit review,2,2,0,"S1, S4","S1, S4",
mechanical-review,SW_DIP6,,DIP switch,select exact substitute after circuit review,1,1,0,S3,S3,
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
